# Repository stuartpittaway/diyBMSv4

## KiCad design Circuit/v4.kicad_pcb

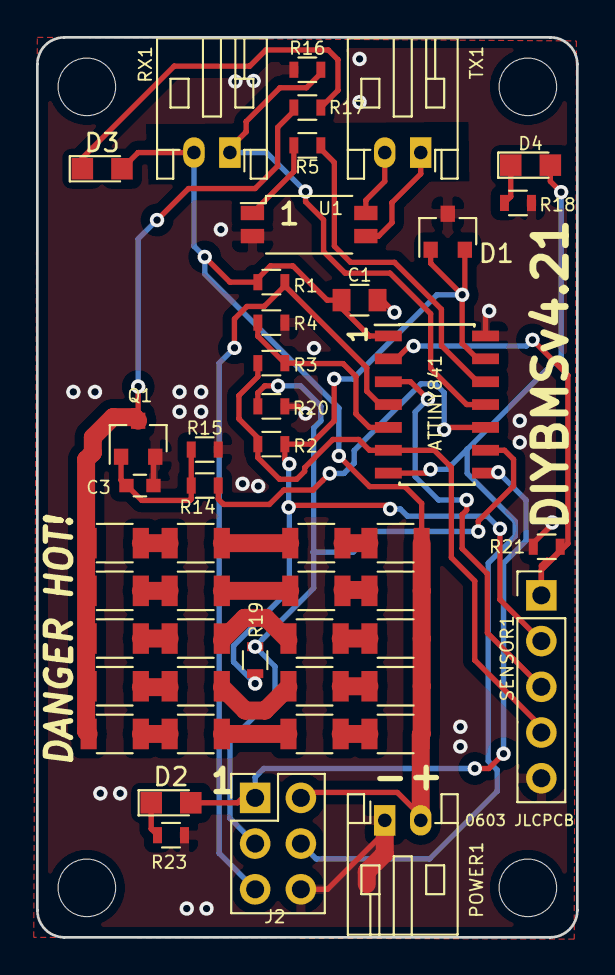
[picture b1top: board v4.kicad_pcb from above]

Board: 2 copper layers, 30.0 x 50.0 mm, 48 parts (0 on the bottom side), 37 nets.

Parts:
ATTINY841: ATtiny841-SSU; SOIC-14_3.9x8.7mm_Pitch1.27mm
C1: 100nF; C_0805
C3: 10uF X5R; C_0603
D1: AZ432ANTR-E1; SOT-23
D2: Blue; LED_0805
D3: Red; LED_0805
D4: Green; LED_0805
J2: AVR-ISP-6; Pin_Header_Straight_2x03_Pitch2.54mm
POWER1: Battery; JST_PH_S2B-PH-K_02x2.00mm_Angled
Q1: AO3400A; SOT-23
R1: 10KOHMS; R_0603
R2: 1KOHMS; R_0603
R3: 68KOHMS; R_0603
R4: 27KOHMS; R_0603
R5: 220OHMS; R_0603
R6, R7, R8, R9, R10, R11, R12, R13, R22, R24, R25, R26, R27, R28, R29, R30, R31, R32, R33, R34: 6.2OHMS; R_1206
R14: 510OHMS; R_0603
R15, R20, R21: 47KOHMS; R_0603
R16: 4.7KOHMS; R_0603
R17, R18: 2.2KOHMS; R_0603
R19: NCP18WB473J03RB; R_0603
R23: 1.8KOHMS; R_0603
RX1: RX Connector; JST_PH_S2B-PH-K_02x2.00mm_Angled
SENSOR1: Remote temp input 47K @ 25oC; Pin_Header_Straight_1x05_Pitch2.54mm
TX1: TX Connector; JST_PH_S2B-PH-K_02x2.00mm_Angled
U1: EL3H7(B)(TA)-G; SOP-4_4.4x2.8mm_Pitch1.27mm

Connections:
2_VOLT: ATTINY841.13, D1.1, D1.2, R2.2, R19.1, SENSOR1.2
DUMP_LOAD_ENABLE: ATTINY841.10, R14.2
ENABLE: ATTINY841.6, R2.1, R3.1, SENSOR1.4
GND: ATTINY841.14, C1.2, C3.2, D1.3, J2.6, POWER1.1, Q1.2, R4.2, R15.2, R16.1, R18.1, R20.2, R21.2, R23.1, SENSOR1.5, U1.2
unnamed: ATTINY841.2, R21.1, SENSOR1.1
unnamed: ATTINY841.3, SENSOR1.3
unnamed: ATTINY841.4, J2.5, R1.2
unnamed: ATTINY841.5, R3.2, R4.1
unnamed: ATTINY841.7, D4.2, J2.4
unnamed: ATTINY841.8, D2.2, J2.1
unnamed: ATTINY841.9, J2.3, R19.2, R20.1
unnamed: C3.1, Q1.1, R14.1, R15.1
unnamed: D2.1, R23.2
unnamed: D3.1, R17.2
unnamed: D4.1, R18.2
unnamed: Q1.3, R12.2, R13.2, R17.1, R29.2, R30.2, R34.2
unnamed: R5.1, U1.1
unnamed: R6.2, R8.1
unnamed: R7.2, R9.1
unnamed: R8.2, R10.1
unnamed: R10.2, R12.1
unnamed: R9.2, R11.1
unnamed: R11.2, R13.1
unnamed: R22.2, R25.1
unnamed: R24.2, R26.1
unnamed: R25.2, R27.1
unnamed: R26.2, R28.1
unnamed: R27.2, R29.1
unnamed: R28.2, R30.1
unnamed: R31.2, R32.1
unnamed: R32.2, R33.1
unnamed: R33.2, R34.1
unnamed: TX1.1, U1.3
unnamed: TX1.2, U1.4
RXD0: ATTINY841.11, R16.2, RX1.1
TXD0: ATTINY841.12, R5.2
VCC: ATTINY841.1, C1.1, D3.2, J2.2, POWER1.2, R1.1, R6.1, R7.1, R22.1, R24.1, R31.1, RX1.2

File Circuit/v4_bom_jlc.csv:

"Comment","Designator","Footprint","LCSC Part #"
"ATtiny841-SSU","ATTINY841","SOIC-14_3.9x8.7mm_Pitch1.27mm","C219103"
"100nF","C1","C_0805","C49678"
"10uF X5R","C3","C_0603","C19702"
"AZ432ANTR-E1","D1","SOT-23","C84139"
"Blue","D2","LED_0805","C2293"
"Red","D3","LED_0805","C84256"
"Green","D4","LED_0805","C2297"
"AO3400A","Q1","SOT-23","C20917"
"10KOHMS","R1","R_0603","C25804"
"1KOHMS","R2","R_0603","C21190"
"68KOHMS","R3","R_0603","C23231"
"27KOHMS","R4","R_0603","C22967"
"220OHMS","R5","R_0603","C22962"
"510OHMS","R14","R_0603","C23193"
"47KOHMS","R15,R20,R21","R_0603","C25819"
"4.7KOHMS","R16","R_0603","C23162"
"2.2KOHMS","R18,R17","R_0603","C4190"
"NCP18WB473J03RB","R19","R_0603","C86142"
"1.8KOHMS","R23","R_0603","C4177"
"6.2OHMS","R30,R28,R26,R24,R29,R27,R25,R22,R13,R11,R9,R7,R12,R10,R8,R6,R34,R33,R32,R31","R_1206","C25344"
"EL3H7(B)(TA)-G","U1","SOP-4_4.4x2.8mm_Pitch1.27mm","C32565"

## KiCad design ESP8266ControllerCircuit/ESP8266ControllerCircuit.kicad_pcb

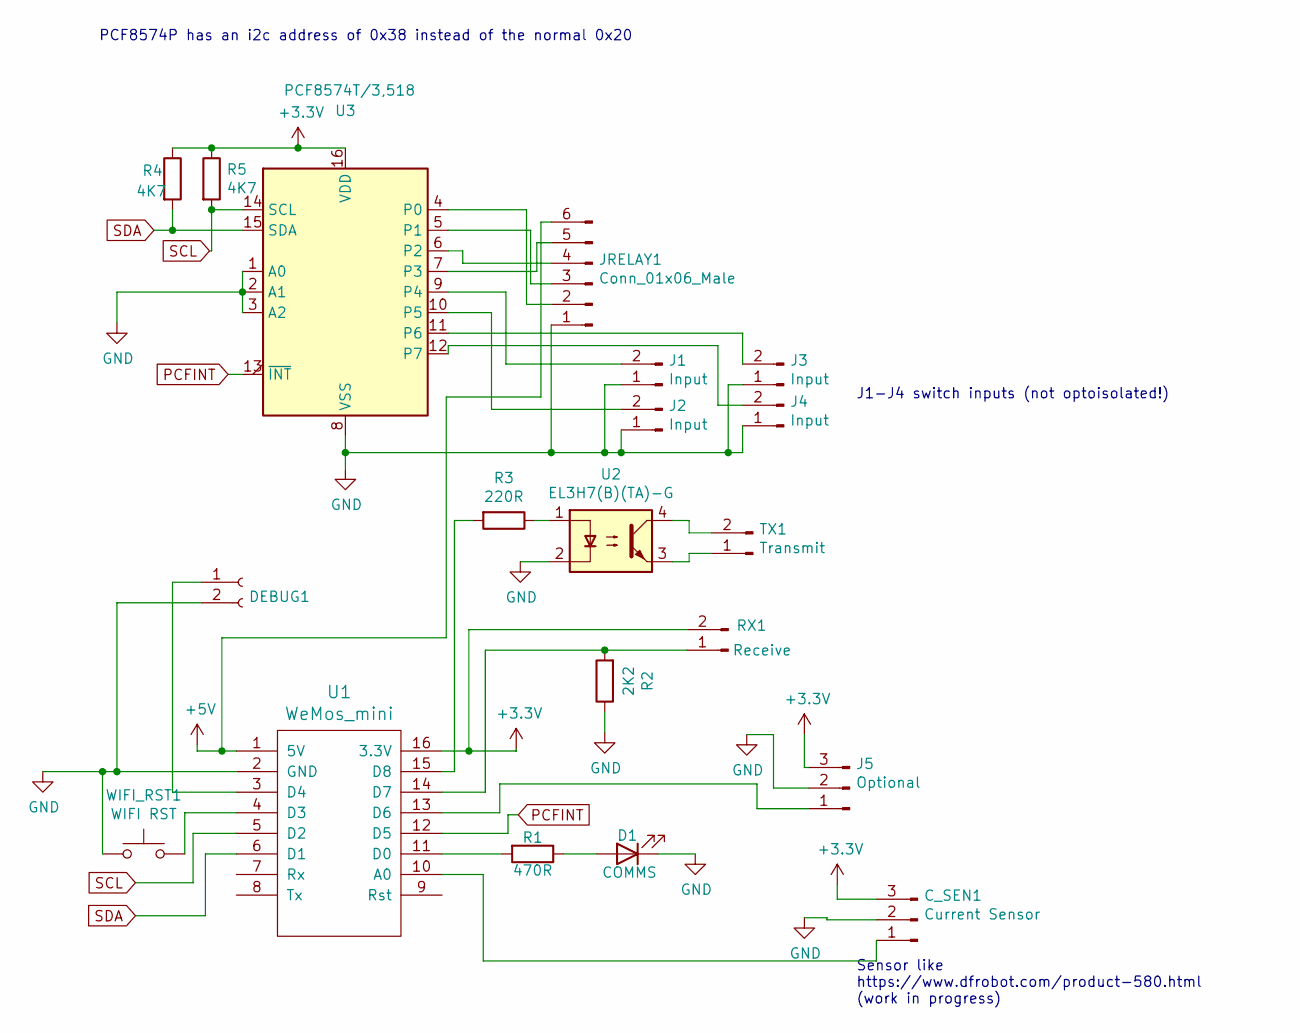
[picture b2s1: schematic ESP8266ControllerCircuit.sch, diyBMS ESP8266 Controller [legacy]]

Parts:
C_SEN1: Current Sensor; Pin_Header_Straight_1x03_Pitch2.54mm
D1: COMMS; LED_0805; PartNumber Hubei KENTO Elec Green 0805; LCSCStockCode C2297
DEBUG1: Conn_01x02_Female; Pin_Header_Straight_1x02_Pitch2.54mm
J1, J2, J3, J4: Input; JST_PH_S2B-PH-K_02x2.00mm_Angled
J5: Optional; Pin_Header_Straight_1x03_Pitch2.54mm
JRELAY1: Conn_01x06_Male; Pin_Header_Straight_1x06_Pitch2.54mm
R1: 470R; R_0805_HandSoldering; PartNumber 0805W8F4700T5E; LCSCStockCode C17710
R2: 2K2; R_0805_HandSoldering; PartNumber 0805W8F2201T5E; LCSCStockCode C17520
R3: 220R; R_0805_HandSoldering; PartNumber 0805W8F2200T5E; LCSCStockCode C17557
R4, R5: 4K7; R_0805_HandSoldering; PartNumber 0805W8F4701T5E; LCSCStockCode C17673
RX1: Receive; JST_PH_S2B-PH-K_02x2.00mm_Angled
TX1: Transmit; JST_PH_S2B-PH-K_02x2.00mm_Angled
U1: WeMos_mini; wemos-d1-mini-with-pin-header
U2: EL3H7(B)(TA)-G; SOP-4_4.4x2.8mm_Pitch1.27mm; LCSCStockCode C32565
U3: PCF8574T/3,518; SOIC-16W_7.5x10.3mm_Pitch1.27mm; PartNumber PCF8574T/3,518; LCSCStockCode C7605
WIFI_RST1: WIFI RST; Pin_Header_Straight_1x02_Pitch2.54mm

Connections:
+3V3: C_SEN1.3, J5.3, R4.1, R5.1, RX1.2, U1.16 (3.3V), U3.16 (VDD)
+5V: JRELAY1.6, U1.1 (5V)
GND: C_SEN1.2, D1.1 (K), DEBUG1.2, J1.1, J2.1, J3.1, J4.1, J5.2, JRELAY1.1, R2.1, U1.2 (GND), U2.2, U3.1 (A0), U3.2 (A1), U3.3 (A2), U3.8 (VSS), WIFI_RST1.1
unnamed: C_SEN1.1, U1.10 (A0)
unnamed: D1.2 (A), R1.1
unnamed: DEBUG1.1, U1.3 (D4)
unnamed: J1.2, U3.9 (P4)
unnamed: J2.2, U3.10 (P5)
unnamed: J3.2, U3.11 (P6)
unnamed: J4.2, U3.12 (P7)
unnamed: J5.1, U1.13 (D6)
unnamed: JRELAY1.2, U3.4 (P0)
unnamed: JRELAY1.3, U3.5 (P1)
unnamed: JRELAY1.4, U3.6 (P2)
unnamed: JRELAY1.5, U3.7 (P3)
unnamed: R1.2, U1.11 (D0)
unnamed: R2.2, RX1.1, U1.14 (D7)
unnamed: R3.1, U2.1
unnamed: R3.2, U1.15 (D8)
unnamed: TX1.1, U2.3
unnamed: TX1.2, U2.4
unnamed: U1.4 (D3), WIFI_RST1.2
PCFINT: U1.12 (D5), U3.13 (~INT~)
SCL: R5.2, U1.5 (D2), U3.14 (SCL)
SDA: R4.2, U1.6 (D1), U3.15 (SDA)

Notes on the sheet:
PCF8574P has an i2c address of 0x38 instead of the normal 0x20
Sensor like https://www.dfrobot.com/product-580.html (work in progress)
J1-J4 switch inputs (not optoisolated!)

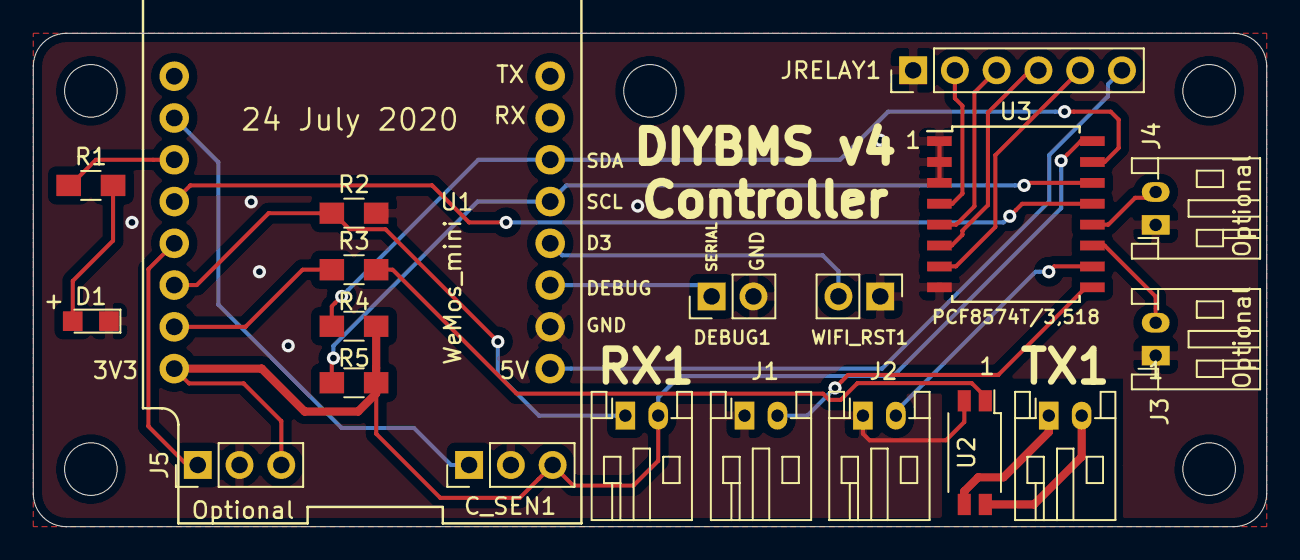
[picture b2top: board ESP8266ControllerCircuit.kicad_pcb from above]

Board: 2 copper layers, 75.0 x 30.0 mm, 20 parts (0 on the bottom side), 25 nets.

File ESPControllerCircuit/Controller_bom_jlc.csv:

Comment,Designator,Footprint,LCSC, LCSC
"Current Sensor","C_SEN1","Pin_Headers:Pin_Header_Straight_1x03_Pitch2.54mm",""
"COMMS","D1","LEDs:LED_D5.0mm",""
"Conn_01x02_Female","DEBUG1","Pin_Headers:Pin_Header_Straight_1x02_Pitch2.54mm",""
"Input","J1,J2,J3,J4","Connectors_JST:JST_PH_S2B-PH-K_02x2.00mm_Angled",""
"Optional","J5","Pin_Headers:Pin_Header_Straight_1x03_Pitch2.54mm",""
"Conn_01x06_Male","JRELAY1","Pin_Headers:Pin_Header_Straight_1x06_Pitch2.54mm",""
"470R","R1","Resistors_SMD:R_0805_HandSoldering","","C17710"
"4K7","R2,R4,R5","Resistors_SMD:R_0805_HandSoldering","","C17673"
"220R","R3","Resistors_SMD:R_0805_HandSoldering","","C17557"
"Receive","RX1","Connectors_JST:JST_PH_S2B-PH-K_02x2.00mm_Angled",""
"Transmit","TX1","Connectors_JST:JST_PH_S2B-PH-K_02x2.00mm_Angled",""
"WeMos_mini","U1","ESPControllerCircuit:wemos-d1-mini-with-pin-header",""
"EL3H7(B)(TA)-G","U2","Package_SO:SOP-4_4.4x2.6mm_P1.27mm","","C32565"
"PCF8574T/3,518","U3","SMD_Packages:SO-16-W","","C7605"
"WIFI RST","WIFI_RST1","Pin_Headers:Pin_Header_Straight_1x02_Pitch2.54mm",""

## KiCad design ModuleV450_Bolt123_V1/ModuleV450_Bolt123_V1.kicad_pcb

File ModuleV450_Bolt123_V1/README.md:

# ModuleV450_Bolt123_V1

DIYBMS v4.5 cell module (ATtiny1624) in the form factor of the BMS_alt board (DIYBMS Lishen/EVE v1.7),
bolted directly onto the cell terminals. EMC-optimised layout.

| Top | Bottom |
|---|---|
|  |  |

*Board assembled by JLCPCB (from the 4-up panel).*

## Ordering at JLCPCB – all files

| What | Single board | 4-up panel (recommended, "Panel by Customer") |
|---|---|---|
| Gerber + drill files | `ModuleV450_Bolt123_V1_gerber_jlc.zip` | `panel4/ModuleV450_Bolt123_V1_panel4_gerber_jlc.zip` |
| Bill of materials (BOM) | `ModuleV450_Bolt123_V1_bom_jlc.csv` | `panel4/ModuleV450_Bolt123_V1_panel4_bom_jlc.csv` |
| Placement file (CPL) | `ModuleV450_Bolt123_V1_cpl_jlc.csv` | `panel4/ModuleV450_Bolt123_V1_panel4_cpl_jlc.csv` |
| Full BOM | `ModuleV450_Bolt123_V1_bom_full.csv` | `panel4/ModuleV450_Bolt123_V1_panel4_bom_full.csv` |

Settings: FR-4, 2 layers, 1.6 mm, 1 oz, green, lead-free HASL, PCB Assembly top side.
Panel: *Panel by Customer*, *Edge Rails/Fiducials*: none, *PCB Qty* = number of panels (5 panels = 20 modules), assembly quantity = number of panels.
Check in the JLC assembly preview: cathode band of D2 towards the VCC side (F1); pin-1 dots of U1, U2 and Q1 at the triangle in the silkscreen.

## Mechanical
| | |
|---|---|
| Board | 154.5 × 31.5 mm |
| Bolt spacing | **123.0 mm** |
| Holes | **6.3 mm** drilled, plated (JLC maximum), Ø 15 mm bare copper ring top + bottom, 16 stitching holes Ø 0.6 mm |
| Left / right | Cell plus (BAT+) / cell minus (GND) |
| Layers | 2, 1.6 mm FR4, 1 oz |

## Layout concept (EMC)
* **Two zones:** quiet zone (plus side, x ≈ 12–48 mm) with MCU, reference D1, optocoupler,
  temperature sensors and connectors. Load zone (x ≈ 51–116 mm) with all 16 load resistors,
  MOSFET Q1 and the minus bolt.
* **Power paths as copper pours instead of tracks:**
  VCC feed 5.8 mm wide along the top edge, VCC bus 5.4 mm,
  series nodes between the resistors 6 × 4.2 mm each, **DRAIN bus 8.3 mm** over the full height
  to all 4 drain pins of Q1, **source pour 14 × 11 mm** from the 3 source pins straight to the minus bolt.
  Remaining power tracks 1.5 mm.
* **Load current return:** Q1 source → copper pour (top) → minus bolt.
  The switched load current does not flow through the MCU ground plane.
* **Star-point supply:** the MCU has its own supply branch
  (F1 → TVS D2 → C2 10 µF → C1 100 nF → U2 pin 1). It is not tapped from the load bus,
  so the ADC does not see the voltage drop caused by the balancing current.
* **Bottom side:** continuous GND plane as reference and shield, connected to the load path only at the
  minus bolt (star point).
* Distance MCU ↔ load block ≈ 20 mm, MCU ↔ Q1 ≈ 65 mm.
* The board temperature sensor R32 sits deliberately at the edge of the quiet zone, right next to the load block.

## Electrical
* Load: **16 × 1.2 Ω 2512 (1 W, UniOhm 25121WF120KT4E, LCSC C46193)** – same resistors as BMS_alt.
  4 strings of 4 in series, in parallel = **1.2 Ω** (BMS_alt is 1.2 Ω in total as well) → **same current as the old board**:
  3.2 V: 2.6 A / 8.5 W · 3.4 V: 2.8 A / 9.6 W · **3.65 V: 3.0 A / 11.1 W** (0.69 W per resistor).
  Set `-DLOAD_RESISTANCE=1.20` in the firmware (see Firmware).
* **Q1 = AO4402** (SO-8, 20 V, 20 A, R_DS(on) max 7 mΩ at V_GS = 2.5 V, LCSC C115828)
  instead of AO3400A (SOT-23) or LONTEN LNG045R210 (TO-252, BMS_alt). ≈ 63 mW loss at 3 A; fully enhanced even at LiFePO4 cell voltage (V_GS ≈ 3 V).
  Gate via R35 510 Ω, pull-down R36 10 kΩ (as V450).
* **F1 = LUTE 2920L500/30GR** (PTC 2920, 5 A hold / 10 A trip, 30 V, 5 mΩ, LCSC/JLC C19078763, ≈ $0.16)
  instead of mSMD150. Still holds ≈ 3.5 A at 60–70 °C, i.e. above the max. balancing current of 3.0 A
  (the BMS_alt had only 3 A hold = right at the limit). Voltage drop at 3 A ≈ 15 mV.
* **Comms: TX1/RX1 = Molex PicoBlade 53261-0271** (1.25 mm, 2-pin, SMD right angle, LCSC C177225), matching the
  "Mini Micro JST 1.25 mm" cables. Connector opening towards the bottom edge, assembled by JLC.
  Pin 1 TX: TXOUT1 / pin 2: TXOUT2 · RX: pin 1 RXD0 / pin 2 VCC (as V450).
* Cell temperature: NTC R23 at the bottom edge right next to the plus bolt; on the bottom side a copper area on the
  plus terminal underneath acts as a thermal bridge.
  **R23B** = assembly option (not fitted, same nets PA3/ENABLE) right at the load block, left of the
  VCC bus. Fit R23 **or** R23B, not both.
* **V450 parts not available at JLCPCB replaced (JLC stock checked 2026-10-08):**
  D1 AZ432ANTR-E1 → **TI TLV431BQDBZR (C398374)**, 1.24 V ±0.5 %, −40…125 °C,
  SOT-23 pin 1 REF / pin 2 cathode (both VREF) / pin 3 anode (GND) – fits without layout change;
  reference 1.24 V instead of 1.25 V → calibrate the module.
* **Cost (JLC Basic instead of Extended parts, saves the €2.76 setup fee each):** R5 180 Ω → **200 Ω (C17540)**,
  optocoupler current ≈ 10 mA · D4 → **yellow 0805 (C2296)**, V_F 1.8–2.4 V, still lights at low cell voltage ·
  U1 → **Lite-On LTV-217-B-G (C115450)**, 4-pin mini-flat 1.27 mm, pin 1 A / 2 K / 3 E / 4 C as EL3H7.
* Renamed compared with V450: R14→R35, R15→R36, R16→R30, R17→R37, R18→R34, R19→R32, R20→R33, R21→R31;
  load resistors R6–R21.

## Firmware (diyBMSv4ESP32 / ATTINYCellModule, environment V450)
* The reference voltage is hard-coded: `CellVoltage()` computes `V_cell = 1250 mV × 65535 / ADC × Calibration`
  (`packet_processor.cpp`; the reference on pin PA5 is measured against VDD).
* D1 TLV431BQ delivers 1.24 V instead of 1.25 V → without calibration the module reads ≈ 0.8 % high (≈ +27 mV at 3.3 V).
  Correction without new firmware: set the calibration factor of each module in the controller to ≈ **0.992**
  (adjust with a multimeter; allowed range 0.8–10, default 1.0).
  Alternatively change 1250L → 1240L in `packet_processor.cpp`.
* In `platformio.ini` (environment V450) change **`-DLOAD_RESISTANCE=3.30` → `1.20`**, otherwise balancing current
  and energy are displayed wrongly in the controller (the value is only used for that).
* Programming: UPDI (header UPDI1: pin 1 VCC, pin 2 UPDI, pin 3 GND), e.g. SerialUPDI with a USB-TTL adapter
  (TX via 470 Ω to UPDI, RX direct to UPDI) and `pymcuprog` or PlatformIO `upload_protocol = serialupdi`.

## Verification
KiCad DRC: 0 errors, 0 unconnected items (silkscreen warnings only).

## Files
* `ModuleV450_Bolt123_V1_gerber_jlc.zip` – Gerber + drill files for JLCPCB (single files in `gerbers/`)
* `ModuleV450_Bolt123_V1_bom_jlc.csv` / `_cpl_jlc.csv` – SMT assembly top side
* `ModuleV450_Bolt123_V1_bom_full.csv` – full BOM
* `ModuleV450_Bolt123_V1_schematic.pdf` / `.svg` – schematic
* `ModuleV450_Bolt123_V1.kicad_pcb` / `.kicad_pro` – KiCad 7 layout

Hand assembly: optional UPDI1 only, and R23B (instead of R23) if wanted.

## 4-up panel for JLCPCB ("Panel by Customer")
A ready-made panel is in `panel4/`. "Panel by JLCPCB" is not offered because of the rounded ends.

| | |
|---|---|
| Content | **4 × ModuleV450_Bolt123_V1** stacked |
| Size | **154.5 × 146.0 mm** |
| Separation | 2 mm milled slot, 3 tabs of 5 mm per long edge (at x = 5 / 73 / 118 mm, straight edge between the bolts) with 7 breakaway holes Ø 0.5 mm (mouse bites); copper pulled back 0.7 mm at the tabs, no tracks at the tabs |
| Rails | 5 mm top and bottom, with 3 tooling holes Ø 1.152 mm (JLC standard, asymmetric) and 3 fiducials (1 mm copper, 2 mm mask opening) |
| Assembly | `ModuleV450_Bolt123_V1_panel4_bom_jlc.csv` + `_cpl_jlc.csv`, designators R1_1 … R1_4 (panel position 1 = top) |

**Ordering 20 modules at JLC:**
* Gerber: `ModuleV450_Bolt123_V1_panel4_gerber_jlc.zip`
* *Panel Format*: **Panel by Customer**, *Different Design*: 1, *Edge Rails/Fiducials*: **none** (already in the panel)
* *PCB Qty*: **5** (panels) → 20 modules
* PCB Assembly: quantity 5, BOM and CPL from `panel4/`

## JLCPCB notes
* D2 (SMB, SMBJ5.0A C440263): the JLC model matches KiCad → no CPL rotation offset; the cathode band must be on the VCC side (pad 1) (checked in the JLC preview 2026-10-09).
* U1 (SOP-4, LTV-217): the JLC part model is rotated 180° against KiCad → CPL rotation +180° (checked in the JLC preview 2026-10-09).
* TX1/RX1 (PicoBlade): the JLC model is rotated 180° against KiCad → CPL rotation +180°.
* CPL positions = centre of the copper pads (this is how JLC places parts). For the PicoBlade TX1/RX1 the KiCad origin is 0.6 mm off the pad centre; without this correction the connector stuck out over the board edge in the JLC preview.

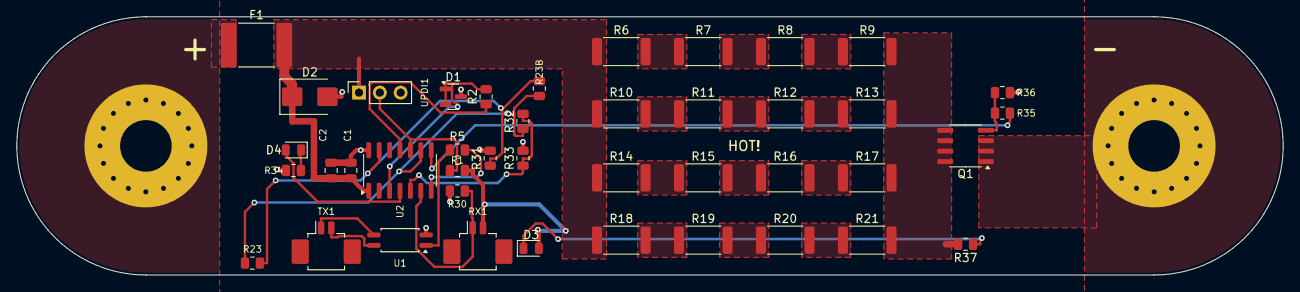
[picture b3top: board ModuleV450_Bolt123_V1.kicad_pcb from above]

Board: 2 copper layers, 154.5 x 31.5 mm, 45 parts (1 on the bottom side), 32 nets.

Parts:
BAT+: M6 bolt 6.3mm
BAT-: M6 bolt 6.3mm
C1: 100nF; C_0805_2012Metric
C2: 10uF; C_0805_2012Metric
D1: TLV431BQDBZR; SOT-23
D2: SMBJ5.0A; D_SMB
D3: Red; LED_0805_2012Metric
D4: Yellow; LED_0805_2012Metric
F1: 2920L500 5A; Fuse_2920_7451Metric
G1: LOGO; diybms_logo_24x10mm
Q1: AO4402; SOIC-8_3.9x4.9mm_P1.27mm
R1: 100K; R_0805_2012Metric
R2: 1K; R_0805_2012Metric
R5: 180R; R_0805_2012Metric
R6, R7, R8, R9, R10, R11, R12, R13, R14, R15, R16, R17, R18, R19, R20, R21: 1R2; R_2512_6332Metric
R23, R32: NTC 10K B3950; R_0805_2012Metric
R23B: NTC 10K B3950 DNP; R_0805_2012Metric
R30, R34, R37: 2K2; R_0805_2012Metric
R31, R33, R36: 10K; R_0805_2012Metric
R35: 510R; R_0805_2012Metric
RX1: RX; Molex_PicoBlade_53261-0271_1x02-1MP_P1.25mm_Horizontal
TX1: TX; Molex_PicoBlade_53261-0271_1x02-1MP_P1.25mm_Horizontal
U1: EL3H7(B)(TA)-G; SOP-4_4.4x2.6mm_P1.27mm
U2: ATTINY1624-SSU; SOIC-14_3.9x8.7mm_P1.27mm
UPDI1: UPDI; PinSocket_1x03_P2.54mm_Vertical

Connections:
BAT+: BAT+.1, F1.1
DRAIN: Q1.5, Q1.6, Q1.7, Q1.8, R9.2, R13.2, R17.2, R21.2, R37.2
DUMP: R35.1, U2.8
ENABLE: R23.1, R23B.1, R32.1, U2.9
GATE: Q1.4, R35.2, R36.2
GND: BAT-.1, C1.2, C2.2, D1.3, D2.2, Q1.1, Q1.2, Q1.3, R30.1, R31.2, R33.2, R34.1, R36.1, U1.2, U2.14, UPDI1.3
LED_B: D4.1, R34.2
LED_R: D3.1, R37.1
OPTO_A: R5.1, U1.1
PA3: R23.2, R23B.2, R31.1, U2.13
PA6: D4.2, U2.4
PA7: R32.2, R33.1, U2.5
REF_EN: R2.1, U2.11
RESET: R1.2, U2.10, UPDI1.2
RXD0: R30.2, RX1.1, U2.6
S1_1: R6.2, R7.1
S1_2: R7.2, R8.1
S1_3: R8.2, R9.1
S2_1: R10.2, R11.1
S2_2: R11.2, R12.1
S2_3: R12.2, R13.1
S3_1: R14.2, R15.1
S3_2: R15.2, R16.1
S3_3: R16.2, R17.1
S4_1: R18.2, R19.1
S4_2: R19.2, R20.1
S4_3: R20.2, R21.1
TXD0: R5.2, U2.7
TXOUT1: TX1.1, U1.3
TXOUT2: TX1.2, U1.4
VCC: C1.1, C2.1, D2.1, D3.2, F1.2, R1.1, R6.1, R10.1, R14.1, R18.1, RX1.2, U2.1, UPDI1.1
VREF: D1.1, D1.2, R2.2, U2.3

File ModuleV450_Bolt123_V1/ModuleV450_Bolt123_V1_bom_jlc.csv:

"Comment","Designator","Footprint","LCSC Part #"
"100nF","C1","C_0805_2012Metric","C49678"
"10uF","C2","C_0805_2012Metric","C15850"
"TLV431BQDBZR","D1","SOT-23","C398374"
"SMBJ5.0A","D2","D_SMB","C440263"
"Red","D3","LED_0805_2012Metric","C84256"
"Yellow","D4","LED_0805_2012Metric","C2296"
"2920L500/30GR 5A","F1","Fuse_2920_7451Metric","C19078763"
"AO4402","Q1","SOIC-8_3.9x4.9mm_P1.27mm","C115828"
"100K","R1","R_0805_2012Metric","C149504"
"1K","R2","R_0805_2012Metric","C17513"
"200R","R5","R_0805_2012Metric","C17540"
"1R2","R6,R7,R8,R9,R10,R11,R12,R13,R14,R15,R16,R17,R18,R19,R20,R21","R_2512_6332Metric","C46193"
"NTC 10K B3950","R23,R32","R_0805_2012Metric","C51597"
"2K2","R30,R34,R37","R_0805_2012Metric","C17520"
"10K","R31,R33,R36","R_0805_2012Metric","C17414"
"510R","R35","R_0805_2012Metric","C17734"
"PicoBlade 2P","RX1,TX1","Molex_PicoBlade_53261-0271_1x02-1MP_P1.25mm_Horizontal","C177225"
"LTV-217-B-G","U1","SOP-4_4.4x2.6mm_P1.27mm","C115450"
"ATTINY1624-SSU","U2","SOIC-14_3.9x8.7mm_P1.27mm","C5160891"

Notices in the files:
Circuit/v4.kicad_pcb:
©2019/2020 Stuart Pittaway
